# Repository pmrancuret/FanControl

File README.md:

#Fan Control

*This project is still a work in progress, so the contents are incomplete*

This project contains everything needed to create a Fan Control board.  This board is used to operate two cooling fans to regulate temperature in an enclosed environment.  In our case, it is going to be used to keep a Playstation cool, inside an enclosed cabinet.  The fans are positioned over holes in the back of the cabinet.

Please feel free to contact me with questions, comments, suggestions, or contributions!

## Contents
* [Features and Specifications] (#features)
* [Parts List] (#partslist)
* [Operation Manual] (#operation)
* [Software Load Instructions] (#swload)

# <a name="features"/>Features and Specifications

## Fan Control board is used to power and control two PC fans, independently.

* Works with two standard 3-wire PC fans.
	* Pin 1 is ground.
	* Pin 2 is fan voltage.
	* Pin 3 is hall-effect sensor (for speed feedback).
* May be used with only one fan if desired.
* Continuous current rating of up to 540mA on each fan.
* Combined power rating of two fans is 6 Watts.
	* This power is limited by wall adapter power rating.
	* Using a 12V supply rated at >= 14.2 Watts would allow up to a combined fan power rating of 13 Watts.
* User may specify maximum fan voltage range.
	* Minimum fan voltage >= 3V.
	* Maximum fan voltage <= 12V.
* Speed of each fan is measured independently using hall-effect sensor feedback.
	* Minimum measurable speed of TBD rpm.
	* Maximum measurable speed of TBD rpm.
* Master On/Off switch provided at board input.

## Arduino mini used for control logic.
* An LCD screen and three pushbuttons are provided to allow the user to provide input settings and view status info.
	* Two buttons used as up/down for scrolling through menu items and adjusting values.
	* One button used as an enter key for making selections.
	* Not pressing any button for 10 seconds will return to default display screen.
* A switch is provided to turn backlight LED on/off.  
* Two potentiometers are provided to allow changing brightness and contrast of screen.
* Default display screen shows both fan speeds and both temperature readings in real-time.
* User may select displayed temperature units (C or F).
* User may change proportional and integral gains for each fan speed control loop.
* User may change various speed, voltage, and temperature limits.
* All settings saved in non-volatile EEPROM.
* User may restore all settings to default values.

## Two independent temperature sensors are used for feedback.  
* User can populate these sensors on-board, or use jumper wires to place them remotely.
* User may select whether to use an average or max temperature for determining fan speeds, or control each fan speed independently using respective temperature sensors.
* User may specify up to 8 point pairs each of the two fan speed vs. temperature lookup tables.
	* Min/Max speed values same as min/max measurable speeds listed above.
	* Minimum temperature value of 0 C.
	* Maximum temperature value of 100 C.
	* Sensor accuracy of +/- 2 C.
	* User may specify table settings with resolution of 0.1 C.
	
## Custom designed PCB.
* Dimensions are 3.1" x 3.9".
* Thickness is 0.062".
* Two-layer board, with only through-hole components for easier soldering (depending who you ask).
* Four mounting holes (0.126" drill) provided in corners.
* Refer to [The Eagle Schematic and Board Files] (https://github.com/pmrancuret/FanControl/tree/master/Schematic_and_Board) for board layout and mounting pattern.

## Custom software.
* Refer to (TBD Code Directory) for code.
* Eclipse (TBD version) used to write and compile software.
* Refer to [Software Load Instructions] (#swload) for instructions on building and loading software into the Arduino mini.

# <a name="partslist"/>Parts List

The following parts were used to assemble this board.  Please refer to [The Eagle Schematic and Board Files] (https://github.com/pmrancuret/FanControl/tree/master/Schematic_and_Board) for information about where each component is used.

Prices in table below are as of Aug 13, 2016.  If you are making this, you may choose to get some extras of some components.  The table below only lists the minimum quantity.  Mounting hardware not included.  PC Fans not included.  Tax/shipping not included.  Money could be saved by using a protoboard instead of making the PCB.  But what's the fun in that?

| Description | Manufacturer | Part Number | Quantity | Cost (each) | Cost (total) |
| ----------- | ------------ | ----------- | -------- | ----------- | ------------ |
| Circuit Board | Pentalogix | [Upload Gerbers] (http://www.pentalogix.com) | 1 | $147.90 | $147.90 |
| Wall Adapter | Sparkfun | [TOL-09442] (https://www.sparkfun.com/products/9442) | 1 | $5.95 | $5.95 |
| Arduino Pro Mini 328 | Sparkfun | [DEV-11113] (https://www.sparkfun.com/products/11113) | 1 | $9.95 | $9.95 |
| LCD Screen | Xiamen Ocular | [GDM1602K] (https://www.sparkfun.com/products/709) | 1 | $15.95 | $15.95 |
| Pushbutton | Sparkfun | [COM-09190] (https://www.sparkfun.com/products/9190) | 3 | $0.50 | $1.50 |
| DC Power Jack | CUI Inc | [PJ-202A] (https://www.sparkfun.com/products/119) | 1 | $1.25 | $1.25 |
| Temperature Sensor | Analog Devices | [TMP37] (http://www.digikey.com/product-detail/en/analog-devices-inc/TMP37FT9Z/TMP37FT9Z-ND/1217626) | 2 | $1.54 | $3.08 |
| Female Break-Away Pin Headers | Sparkfun | [PRT-00115] (https://www.sparkfun.com/products/115) | 1 | $1.50 | $1.50 |
| Male Break-Away Pin headers | Sparkfun | [PRT-00116] (https://www.sparkfun.com/products/116) | 1 | $1.50 | $1.50 |
| 10kOhm, 1/6W, 5% Through-Hole Resistor | Sparkfun | [COM-11508] (https://www.sparkfun.com/products/11508) | 7 | NA | $0.95 |
| 5.1Ohm, 1/4W, 5% Through-Hole Resistor | Yageo | [CFR-25JB-52-5R1] (https://www.digikey.com/product-detail/en/yageo/CFR-25JB-52-5R1/5.1QBK-ND/2238) | 6 | $0.10 | $0.60 |
| 1kOhm, 1/6W, 5% Through-Hole Resistor | Yageo | [CFR-12JB-52-1K] (https://www.digikey.com/product-detail/en/yageo/CFR-12JB-52-1K/1.0KEBK-ND/4000) | 2 | $0.10 | $0.20 |
| 100Ohm, 1/2W Potentiometer | Bourns Inc. | [3362P-1-101LF] (https://www.digikey.com/product-detail/en/bourns-inc/3362P-1-101LF/3362P-101LF-ND/1088410) | 1 | $1.02 | $1.02 |
| 10kOhm, 1/2W Potentiometer | Bourns Inc. | [3362P-1-103LF] (https://www.digikey.com/product-detail/en/bourns-inc/3362P-1-103LF/3362P-103LF-ND/1088412) | 1 | $1.02 | $1.02 |
| 10uF, 25V Through-Hole Ceramic Capacitor | TDK Corporation | [FK16X7R1E106K] (https://www.digikey.com/product-detail/en/tdk-corporation/FK16X7R1E106K/445-8351-ND/2815281) | 7 | $0.63 | $4.41 |
| 1.5mH, 540mA Through-Hole Inductor | Abracon LLC | [AIUR-06-152K] (https://www.digikey.com/product-detail/en/abracon-llc/AIUR-06-152K/AIUR-06-152K-ND/2343620) | 2 | $0.99 | $1.98 |
| P-Channel MOSFET (30V, 650mA) | Microchip Technology | [VP3203N3-G] (https://www.digikey.com/product-detail/en/microchip-technology/VP3203N3-G/VP3203N3-G-ND/4902418) | 2 | $1.37 | $2.74 |
| NPN Transistor (40V, 200mA) | Fairchild Semiconductor | [2N3904BU] (https://www.digikey.com/product-detail/en/fairchild-semiconductor/2N3904BU/2N3904FS-ND/1413) | 2 | $0.18 | $0.36 |
| Shottky Diode (1A) | Fairchild Semiconductor | [1N5817] (https://www.digikey.com/product-detail/en/fairchild-semiconductor/1N5817/1N5817FSCT-ND/1532776) | 2 | $0.43 | $0.86 |
| 5V output DC-DC Converter (2.5W) | Recom Power | [R-78E5.0-0.5] (https://www.digikey.com/product-detail/en/recom-power/R-78E5.0-0.5/945-1648-5-ND/2834904) | 1 | $2.84 | $2.84 |
| Slide Switch | CW Industries | [GF-123-0054] (https://www.digikey.com/product-detail/en/cw-industries/GF-123-0054/CWI333-ND/4089770) | 2 | $0.93 | $1.86 |
| 3-Pin fan connector | TE Connectivity | [640456-3] (https://www.digikey.com/product-detail/en/te-connectivity-amp-connectors/640456-3/A19470-ND/259010) | 2 | $0.13 | $0.26 |
| Total Cost  | | | | | $207.68 |

# <a name="operation"/>Operation Manual

*work in progress*

# <a name="swload"/>Software Load Instructions

*work in progress*

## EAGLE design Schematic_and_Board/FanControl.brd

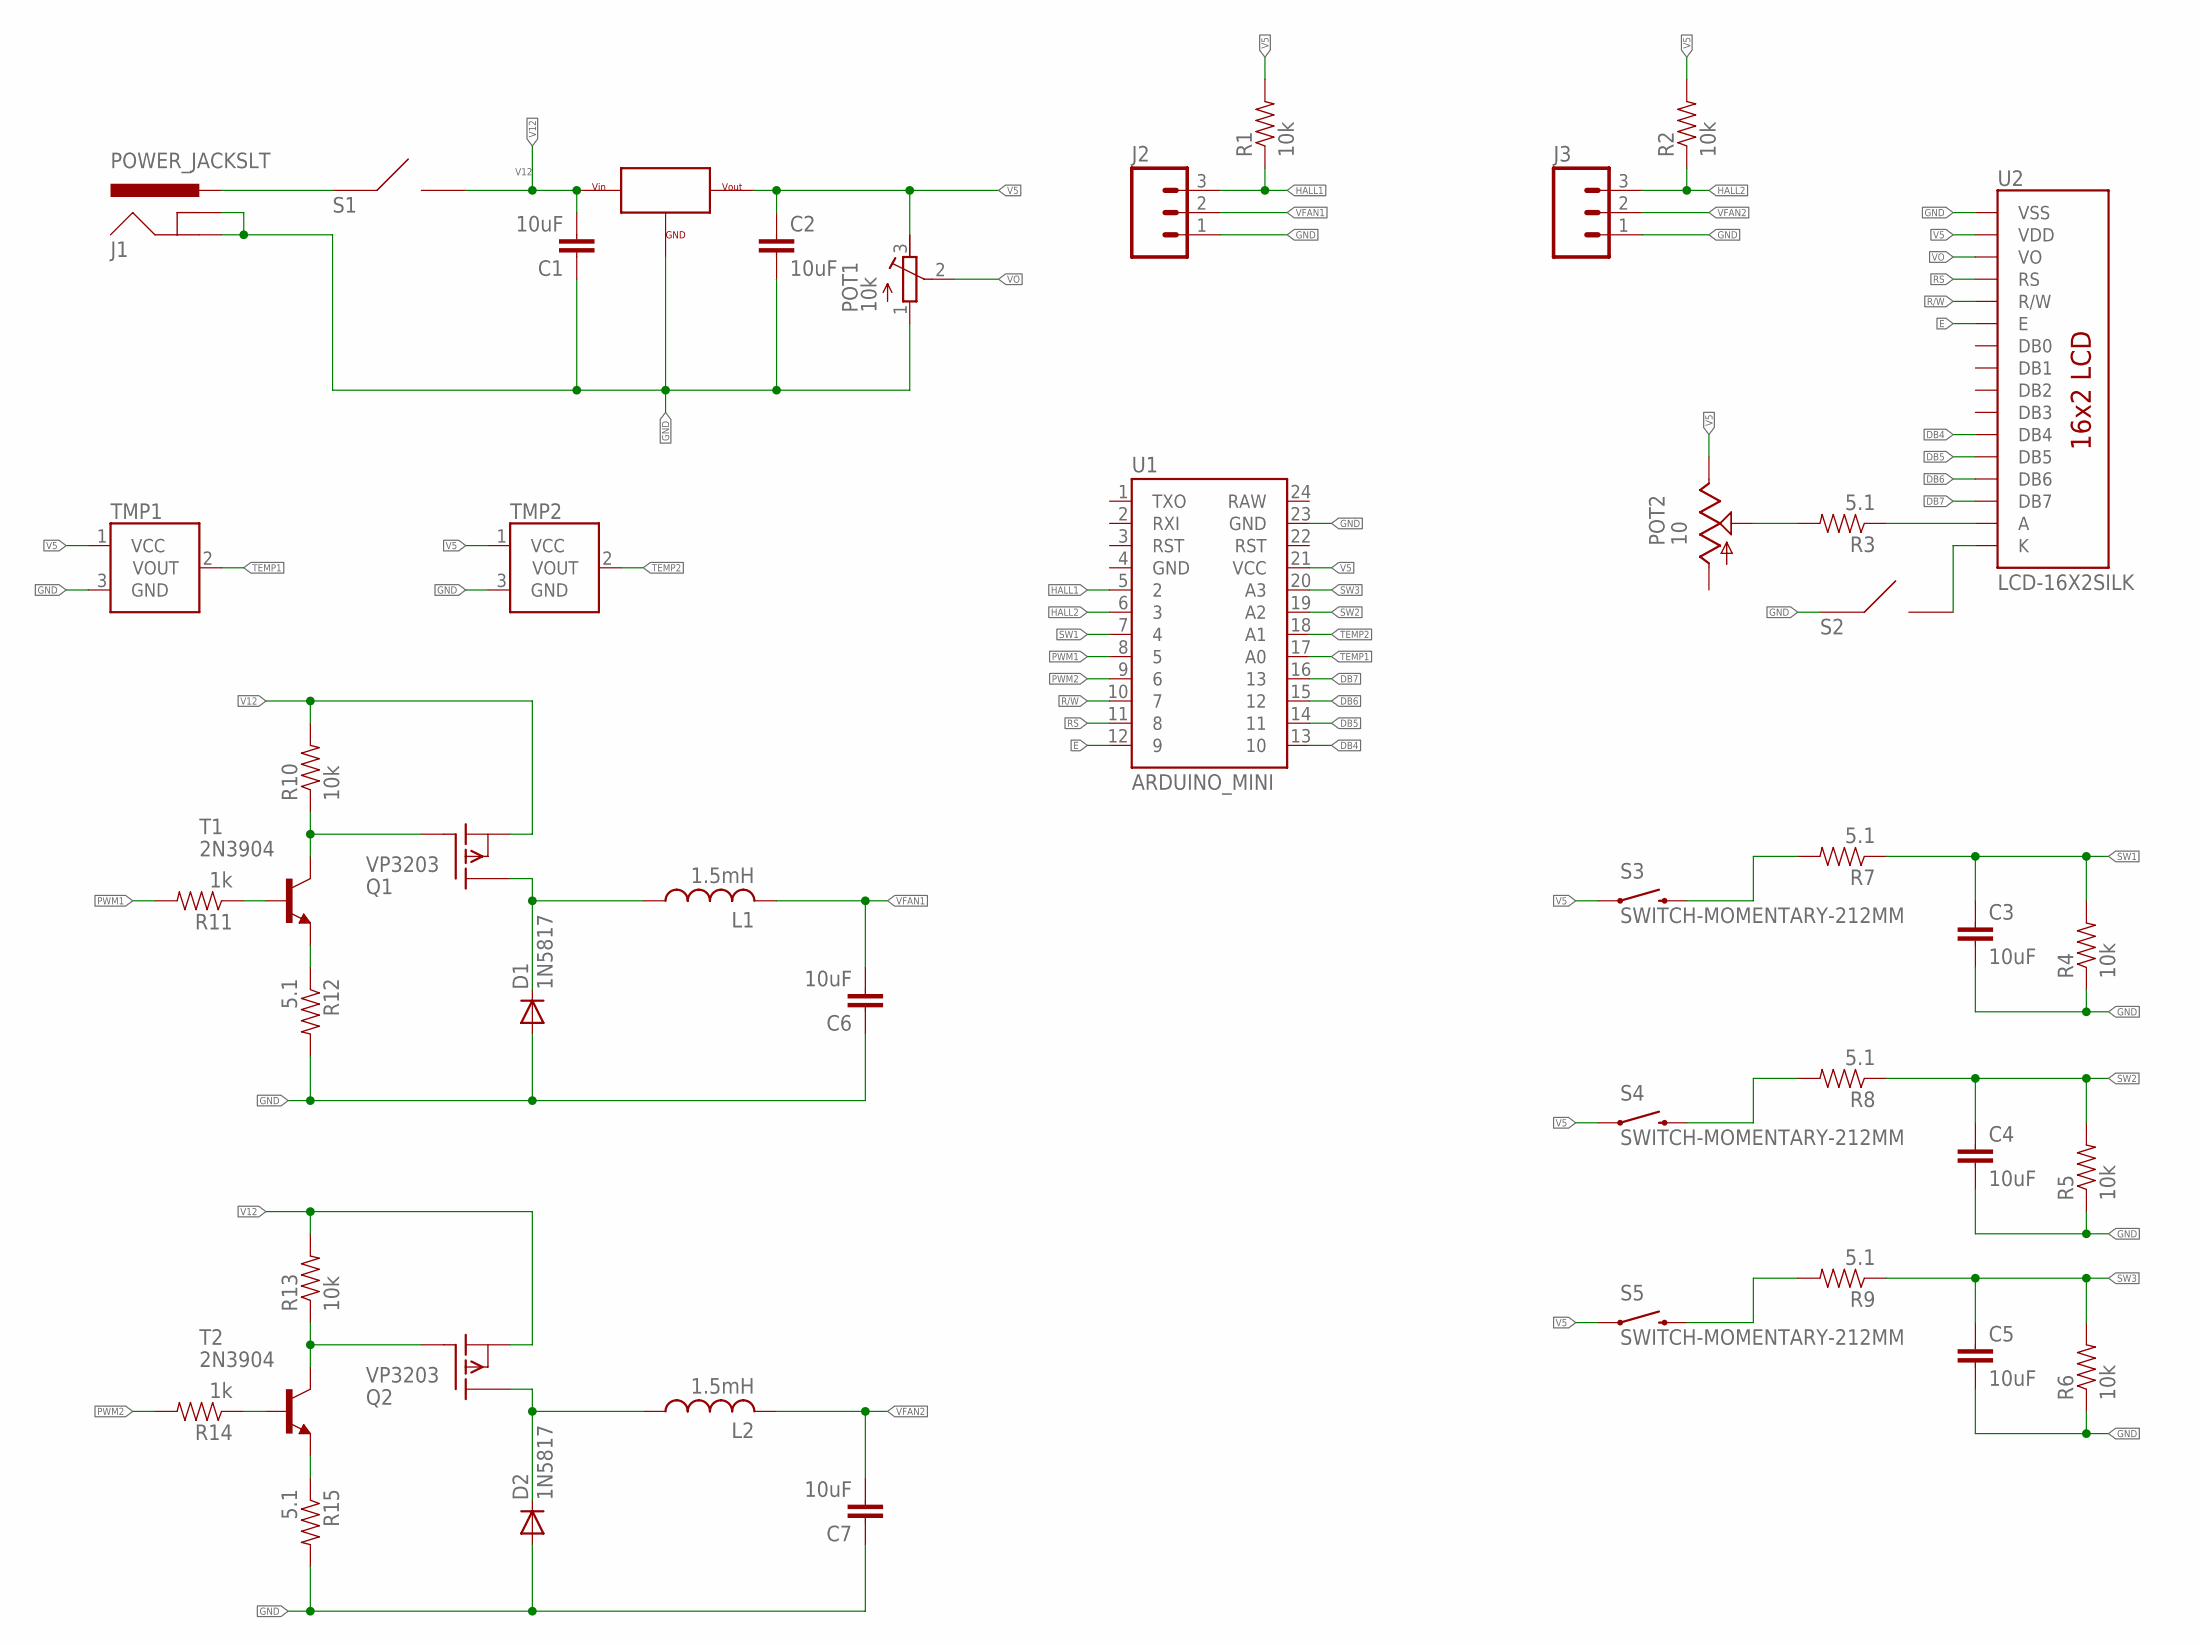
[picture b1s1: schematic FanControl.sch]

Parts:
C1, C2, C3, C4, C5, C6, C7: 10uF; CAP-PTH-5MM
D1, D2: 1N5817; DO41-10
J1: POWER_JACKSLT; POWER_JACK_SLOT
J2, J3: M03POLAR; MOLEX-1X3
L1, L2: 1.5mH; 0204/7
POT1: 10k; RTRIM3362P
POT2: 10; B25P
Q1, Q2: VP3203; TO-92
R1, R2, R4, R5, R6, R10, R13: 10k; 1/6W-RES
R3, R7, R8, R9, R12, R15: 5.1; 1/6W-RES
R11, R14: 1k; 1/6W-RES
S1, S2: SLIDE_SWITCH; TH_SLIDE_SWITCH
S3, S4, S5: SWITCH-MOMENTARY-212MM; TACTILE-PTH-12MM
T1, T2: 2N3904; TO92
TMP1, TMP2: TMP36GT9; TO-92
U1: ARDUINO_MINI
U2: LCD-16X2SILK; LCD-16X2
U$1: R-78EXX-0.5

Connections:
DB4: U1.13 (10), U2.11 (DB4)
DB5: U1.14 (11), U2.12 (DB5)
DB6: U1.15 (12), U2.13 (DB6)
DB7: U1.16 (13), U2.14 (DB7)
E: U1.12 (9), U2.6 (E)
GND: C1.1, C2.2, C3.2, C4.2, C5.2, C6.1, C7.1, D1.A, D2.A, J1.GND@1 (GNDBREAK), J1.GND@2 (GND), J2.1, J3.1, POT1.1, R4.1, R5.1, R6.1, R12.2, R15.2, S2.A, TMP1.3 (GND), TMP2.3 (GND), U1.23 (GND), U2.1 (VSS), U$1.GND
HALL1: J2.3, R1.1, U1.5 (2)
HALL2: J3.3, R2.1, U1.6 (3)
unnamed: POT2.S, R3.2
unnamed: R3.1, U2.15 (A)
unnamed: J1.PWR, S1.A
unnamed: S2.B, U2.16 (K)
unnamed: R7.2, S3.3 (2)
unnamed: R8.2, S4.3 (2)
unnamed: R9.2, S5.3 (2)
unnamed: R12.1, T1.3 (E)
unnamed: Q1.2 (G), R10.1, T1.1 (C)
unnamed: R11.1, T1.2 (B)
unnamed: D1.C, L1.1, Q1.3 (D)
unnamed: Q2.2 (G), R13.1, T2.1 (C)
unnamed: R14.1, T2.2 (B)
unnamed: R15.1, T2.3 (E)
unnamed: D2.C, L2.1, Q2.3 (D)
PWM1: R11.2, U1.8 (5)
PWM2: R14.2, U1.9 (6)
R/W: U1.10 (7), U2.5 (R/W)
RS: U1.11 (8), U2.4 (RS)
SW1: C3.1, R4.2, R7.1, U1.7 (4)
SW2: C4.1, R5.2, R8.1, U1.19 (A2)
SW3: C5.1, R6.2, R9.1, U1.20 (A3)
TEMP1: TMP1.2 (VOUT), U1.17 (A0)
TEMP2: TMP2.2 (VOUT), U1.18 (A1)
V5: C2.1, POT1.3, POT2.E, R1.2, R2.2, S3.1, S4.1, S5.1, TMP1.1 (VCC), TMP2.1 (VCC), U1.21 (VCC), U2.2 (VDD), U$1.VOUT
V12: C1.2, Q1.1 (S), Q2.1 (S), R10.2, R13.2, S1.B, U$1.VIN
VFAN1: C6.2, J2.2, L1.2
VFAN2: C7.2, J3.2, L2.2
VO: POT1.2, U2.3 (VO)

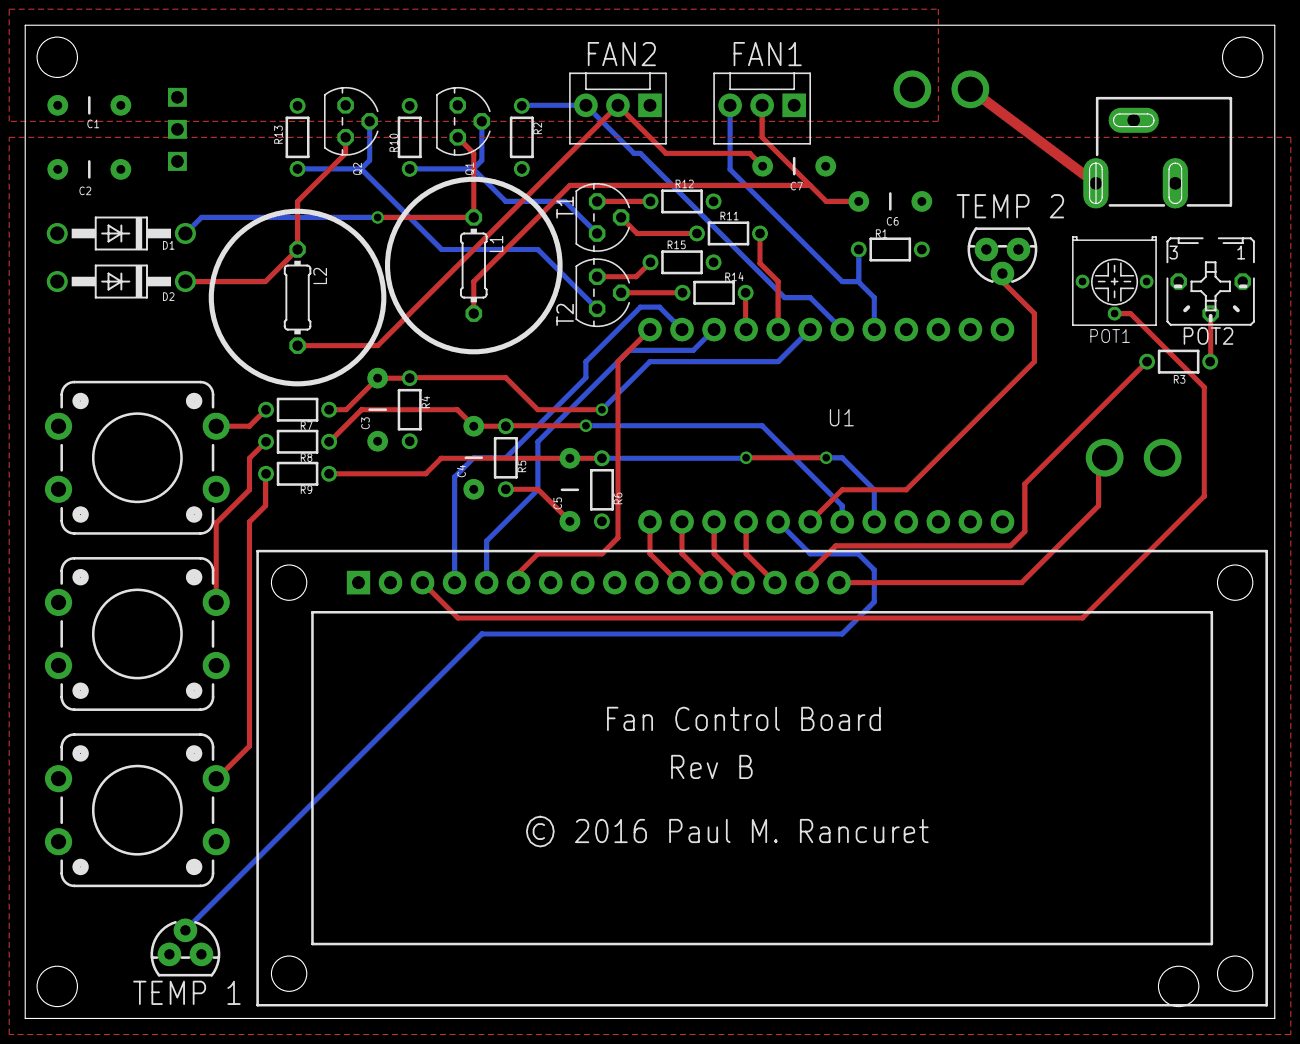
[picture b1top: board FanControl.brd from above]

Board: 2 copper layers, 99.1 x 78.7 mm, 45 parts (0 on the bottom side), 37 nets.

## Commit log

2016-08-13 Add initial schematic, board layout, and gerber files
2016-08-13 Add README file
2016-08-13 Add more detail to README file, and set git to ignore eagle lock files
2016-08-13 Make part list table slightly prettier
2016-08-13 Update git to ignore eagle back-saved files, and job files. Remove those files from the repository, along with the redundant zip file of gerbers.
2016-09-17 initial commit of FanControl Software project
2016-09-18 Add LCD library to project. Rearrange source and include files into src/ and inc/ directories. Add initialization of LCD screen.
2016-09-24 Switch to the built-in Arduino LCD library
2016-10-15 Update Schematic and Board to correct these two errors:
2016-10-16 Update board to revision B. This revision corrects the two errors which were present in Rev A. The first error was that the power jack input ground connection was only made to one of the ground pins 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
2016-10-16 Add pdf version of Rev B schematic.
2016-10-16 Improve loop timing by sampling timer values at start of loop, rather than using a delay in the loop. Add functionality to read hall-effect sensors and calculate fan speeds in RPM. Add a run-time cou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
2016-10-16 Add temperature measurement functionality.
2016-10-17 Add volatile keyword to variables used by ISR. Correct min fan speed so it shows zero when below minimum value.
2016-10-17 Correct overflow problems with temperature scaling. Update temperature and speed display screen to look nicer.
2016-10-23 Update README with up-to-date parts list. Changed the temperature sensor part and the potentiometer used for adjusting screen brightness. Modify .gitignore file to ignore eagle.epf file.
2016-10-23 Remove eagle.epf file from repository
2016-10-23 Update default temp sensor scale/offset values to correspond to the TMP37 sensor from analog devices.
2016-10-29 Add ability to load/save variable values from/to EEPROM. Table of variables in savedVars.h file lists these variables, default values, min/max values, byte size, etc. From this table, these variables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
2016-10-29 Add ability to display temps in F instead of C
2016-10-30 Add PI Control functionality to regulate fan speeds.
2016-11-05 Move many functions to new FanControlUtils.h and FanControlUtils.cpp header and source files to clean up other functions. Add state machine functionality.
2016-11-05 Add reset function for state machine. Add button press reading functionality.
2016-11-05 Rename FanControlUtils to lower-case fanControlUtils for consistency.
2016-11-05 Add debug modes for PI1, PI2, and button presses.
2016-11-05 Adjust LCD screen alignment in button debug mode.
2016-11-05 Increase debug timeout value. correct second line screen printing format in button press debug mode.
2016-11-05 Lower debug timeout to 10 seconds. Add ability to return to normal mode from serial command.
2016-11-05 Change debug PI modes to turn off other fan when debugging one.
2016-11-05 Correct byte order for PI debug modes, and add ability to specify min/max rpm commands.
2016-11-05 Add temp sensor debug mode.
2016-11-06 Add fan speed vs temperature curves for both fans. Add ability to select temperature reading source for each fan (tmp1, tmp2, max, mean). Add interpolation functionality so that fan reference speeds 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
2016-11-06 Add debug state for controlling fan turn-on and turn-off.
2016-11-06 Add debug modes for configuring fan temp-speed lookup tables 1 and 2
2016-11-06 Correct error with displaying table temps 3&4 in lookup table debug modes.
2016-12-28 Set LCD to refresh on loop iterations. Having difficulties with erronious nonsense on screen.

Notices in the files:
Schematic_and_Board/FanControl.brd:
© 2016 Paul M. Rancuret
parts and their libraries:
SparkFun-Capacitors: Licensing: Creative Commons ShareAlike 4.0 International - https://creativecommons.org/licenses/by-sa/4.0
